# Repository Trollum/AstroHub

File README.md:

AstroHub
==================
 First version of my AstroHub. This repo contains eagle PCB files, ready to upload Arduino sketch and source files for GUI.
 
 Device is controlled by Arduino Nano board. There are 2 slots on PCB for LM2596 Step-Down regulator, output on the left one should by set to 5V, the right one you can set as you need.
 
 Application to controll AstroHub can be found here: https://sourceforge.net/projects/astrohub/
 
APT
==================
 APT 3.00 with connected AstroHub shows temperature, humidity and dew point, when DHT22 sensor is connected.
 
 If you have any questions, you can send me a mail: jakub.bartas(na)gmail.com

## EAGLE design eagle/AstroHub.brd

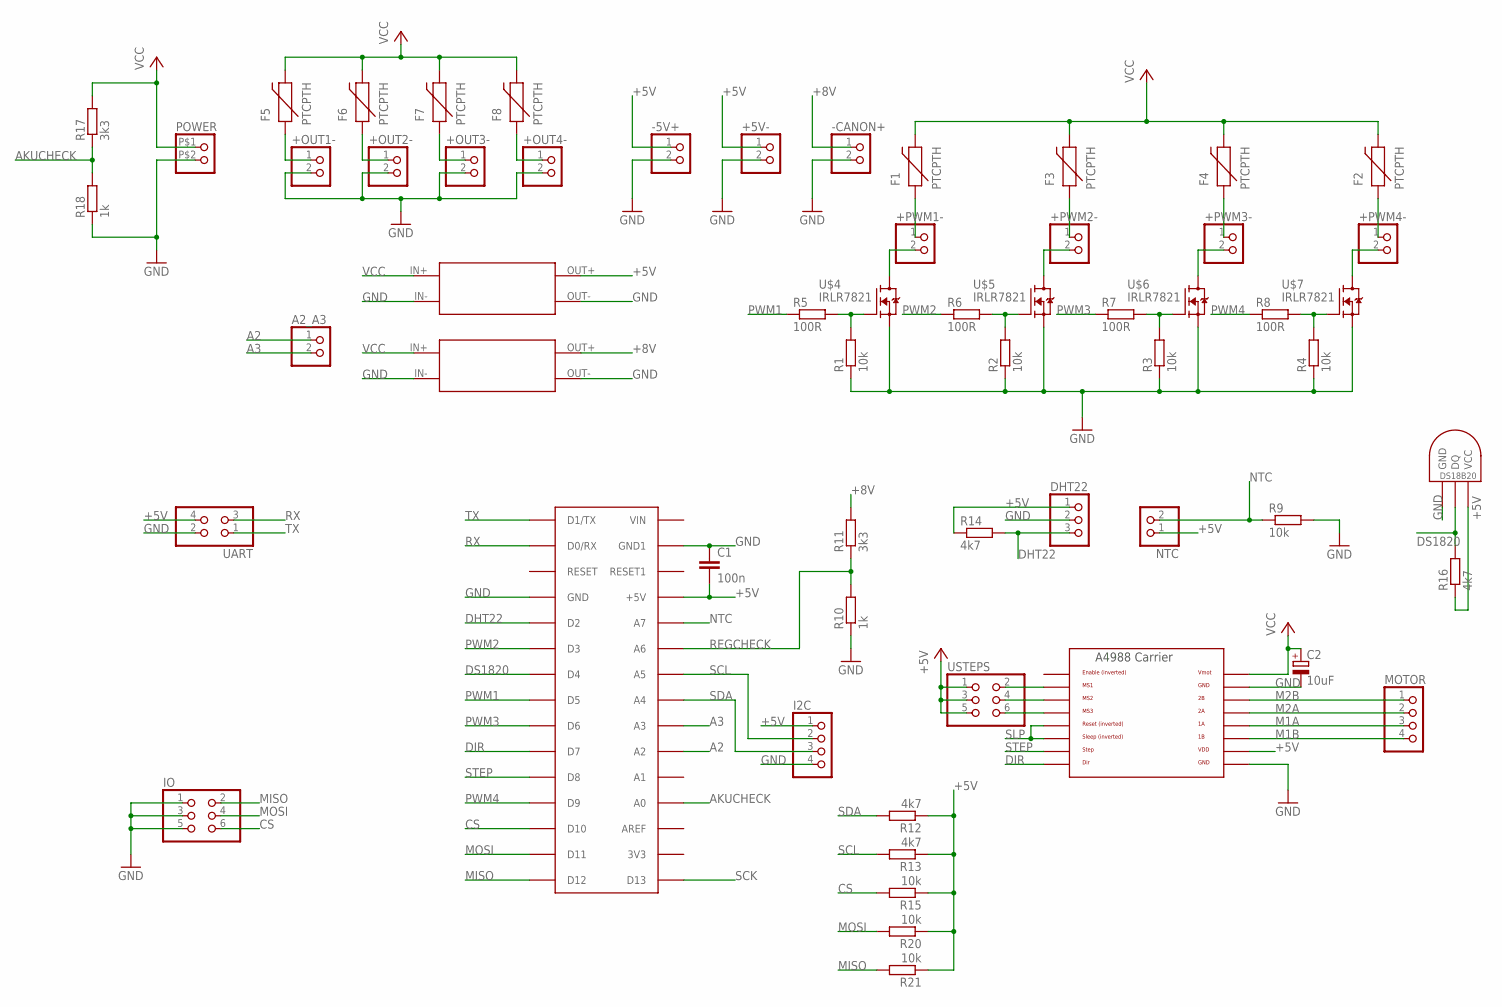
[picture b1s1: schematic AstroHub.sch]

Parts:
+5V-: PINHD-1X2; 1X02
+OUT1-, +OUT2-, +OUT3-, +OUT4-: PINHD-1X2; 1X02
+PWM1-, +PWM2-, +PWM3-, +PWM4-: PINHD-1X2; 1X02
-5V+: PINHD-1X2; 1X02
-CANON+: PINHD-1X2; 1X02
A2_A3: PINHD-1X2; 1X02
C1: 100n; C0603
C2: 10uF; SMC_D
DHT22: PINHD-1X3; 1X03
F1, F2, F3, F4, F5, F6, F7, F8: PTCPTH; PTC
I2C: PINHD-1X4; 1X04
IO: PINHD-2X3; 2X03
MOTOR: PINHD-1X4; 1X04
NTC: PINHD-1X2; 1X02
POWER: PINHD-1X2BIG; 1X02BIG
R1, R2, R3, R4, R9, R15, R20, R21: 10k; R0603
R5, R6, R7, R8: 100R; R0603
R10, R18: 1k; R0603
R11, R17: 3k3; R0603
R12, R13, R14, R16: 4k7; R0603
U$1: ARDUINONANO; PDIP-32
U$2, U$8: LM2596BOARD
U$3: A4988BREAKOUT
U$4, U$5, U$6, U$7: IRLR7821; TO252
U$9: DS1820TO92; DS1820
UART: PINHD-2X2; 2X02
USTEPS: PINHD-2X3; 2X03

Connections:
+5V: +5V-.1, -5V+.1, C1.2, DHT22.1, I2C.1, NTC.1, R12.1, R13.1, R14.1, R15.1, R16.1, R20.1, R21.1, U$1.+5V, U$2.OUT+, U$3.VDD, U$9.VDD (VCC), UART.4, USTEPS.1, USTEPS.3, USTEPS.5
+8V: -CANON+.1, R11.2, U$8.OUT+
A2: A2_A3.1, U$1.A2
A3: A2_A3.2, U$1.A3
AKUCHECK: R17.1, R18.2, U$1.A0
CS: IO.6, R15.2, U$1.D10
DHT22: DHT22.3, R14.2, U$1.D2
DIR: U$1.D7, U$3.DIR
DS1820: R16.2, U$1.D4, U$9.DQ
GND: +5V-.2, +OUT1-.2, +OUT2-.2, +OUT3-.2, +OUT4-.2, -5V+.2, -CANON+.2, C1.1, C2.-, DHT22.2, I2C.4, IO.1, IO.3, IO.5, POWER.P$2 (2), R1.1, R2.1, R3.1, R4.1, R9.2, R10.1, R18.1, U$1.GND, U$1.GND1, U$2.IN-, U$2.OUT-, U$3.GND, U$3.GND@0 (GND), U$4.2 (S), U$5.2 (S), U$6.2 (S), U$7.2 (S), U$8.IN-, U$8.OUT-, U$9.GND, UART.2
M1A: MOTOR.3, U$3.1A
M1B: MOTOR.4, U$3.1B
M2A: MOTOR.2, U$3.2A
M2B: MOTOR.1, U$3.2B
MISO: IO.2, R21.2, U$1.D12
MOSI: IO.4, R20.2, U$1.D11
unnamed: R4.2, R8.2, U$7.1 (G)
unnamed: R3.2, R7.2, U$6.1 (G)
unnamed: R2.2, R6.2, U$5.1 (G)
unnamed: R1.2, R5.2, U$4.1 (G)
unnamed: U$3.MS3, USTEPS.6
unnamed: U$3.MS2, USTEPS.4
unnamed: U$3.MS1, USTEPS.2
unnamed: +PWM1-.1, F1.P$1 (1)
unnamed: +PWM4-.1, F2.P$1 (1)
unnamed: +PWM2-.1, F3.P$1 (1)
unnamed: +PWM3-.1, F4.P$1 (1)
unnamed: +OUT1-.1, F5.P$1 (1)
unnamed: +OUT2-.1, F6.P$1 (1)
unnamed: +OUT3-.1, F7.P$1 (1)
unnamed: +OUT4-.1, F8.P$1 (1)
NTC: NTC.2, R9.1, U$1.A7
P1V: +PWM1-.2, U$4.3 (D)
P2V: +PWM2-.2, U$5.3 (D)
P3V: +PWM3-.2, U$6.3 (D)
P4V: +PWM4-.2, U$7.3 (D)
PWM1: R5.1, U$1.D5
PWM2: R6.1, U$1.D3
PWM3: R7.1, U$1.D6
PWM4: R8.1, U$1.D9
REGCHECK: R10.2, R11.1, U$1.A6
RX: U$1.D0/RX, UART.3
SCK: U$1.D13
SCL: I2C.2, R13.2, U$1.A5
SDA: I2C.3, R12.2, U$1.A4
SLP: U$3.RST, U$3.SLP (SLEEP)
STEP: U$1.D8, U$3.STEP
TX: U$1.D1/TX, UART.1
VCC: C2.+, F1.P$2 (2), F2.P$2 (2), F3.P$2 (2), F4.P$2 (2), F5.P$2 (2), F6.P$2 (2), F7.P$2 (2), F8.P$2 (2), POWER.P$1 (1), R17.2, U$2.IN+, U$3.VMOT, U$8.IN+

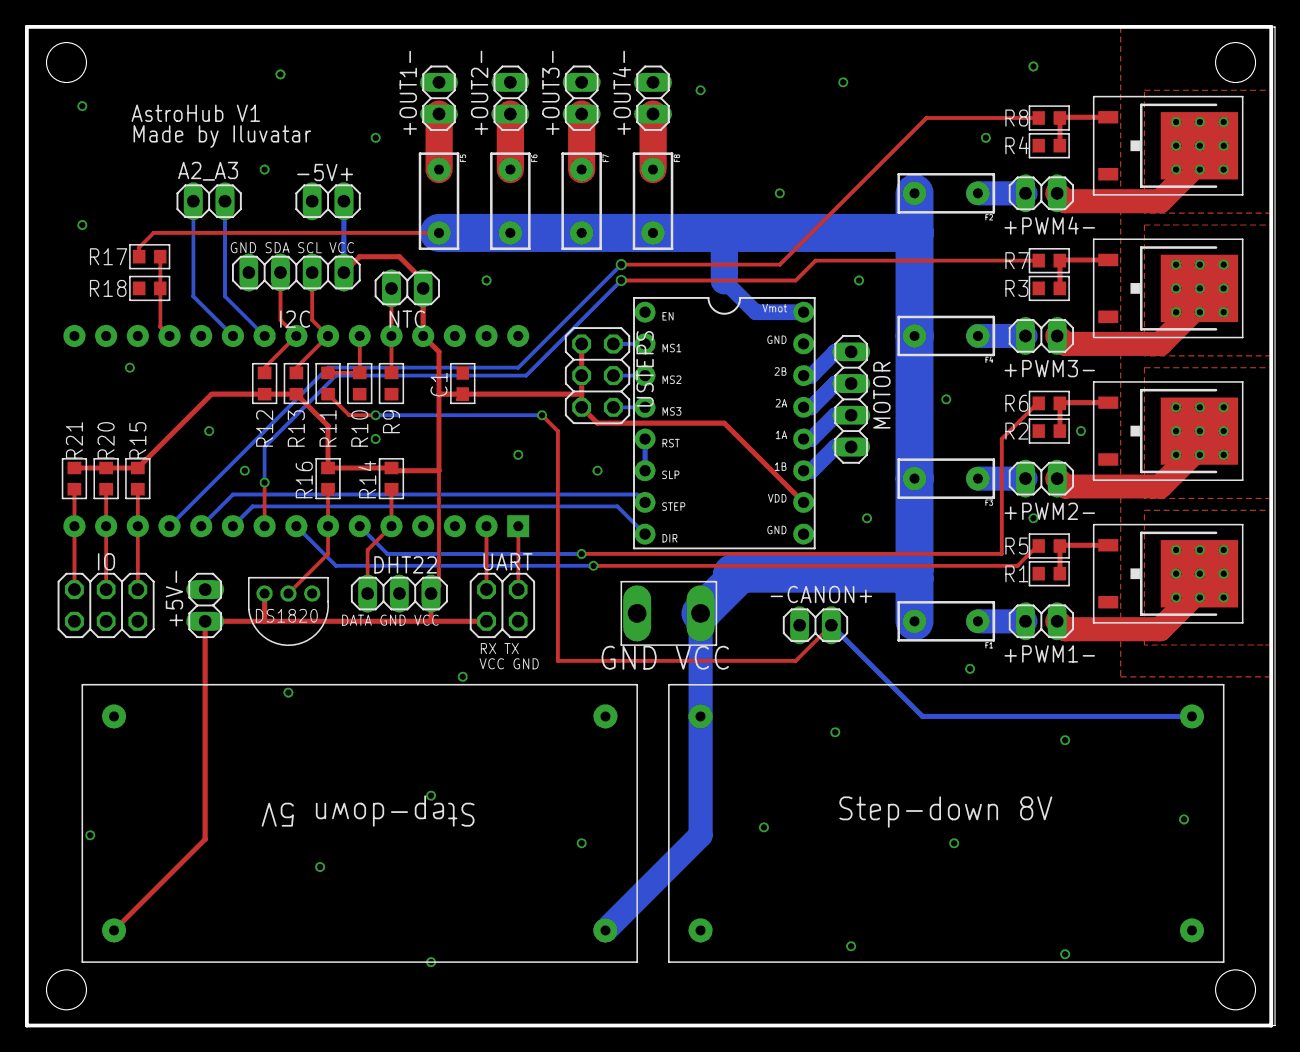
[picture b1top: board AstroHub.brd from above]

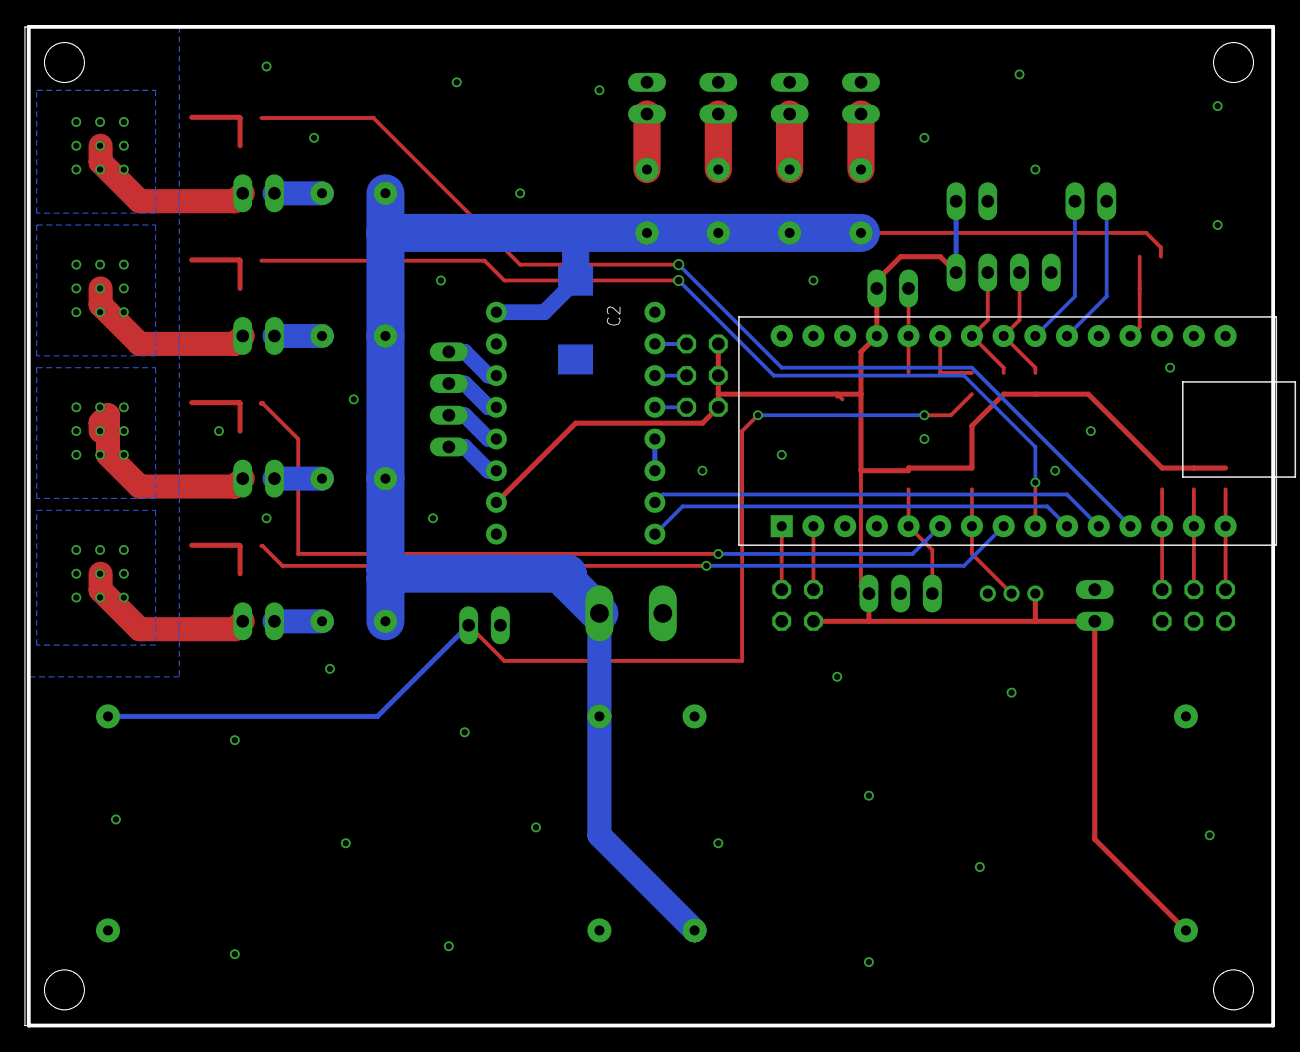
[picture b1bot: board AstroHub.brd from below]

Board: 2 copper layers, 100.0 x 80.0 mm, 59 parts (2 on the bottom side), 48 nets.

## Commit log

2015-08-13 move
2015-08-13 libraries
2015-08-15 NTC disable
2015-08-15 readme fix
2015-08-15 eagle files added
2015-08-16 fixed resistor value
2015-08-16 methods added
    added reverse stepper direction checko box
    added voltage value divider
2015-08-16 added focuser tooltip
2015-08-21 move stepper fix
2015-08-21 fix
    1. write settings immediately after settings dialog opened
    2. turn off PWM after disconnect
2015-08-27 readme
2015-09-03 preparation for ASCOM driver
2015-09-04 ready to ASCOM sketch
2015-09-04 Revert "ready to ASCOM sketch"
    This reverts commit 38b0bea8cebf24403d9adbe06f922cd0d5162ec1.
2015-09-04 ASCOM sources added
2015-09-04 readVoltage method change
    now voltage is determined as mean from 10 measurements
2015-11-09 APT integration test
2015-11-13 APT integration
2015-11-13 thermal pads added
2015-11-13 clean

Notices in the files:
parts and their libraries:
SparkFun-PowerIC: Licensing: Creative Commons ShareAlike 4.0 International - https://creativecommons.org/licenses/by-sa/4.0
